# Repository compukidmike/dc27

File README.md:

# Here's all the design files for both badges we made for Defcon 27

# Kit assembly instructions for the Fifth Element badges are [here](https://github.com/compukidmike/dc27/tree/master/Fifth%20Element%20Badge).

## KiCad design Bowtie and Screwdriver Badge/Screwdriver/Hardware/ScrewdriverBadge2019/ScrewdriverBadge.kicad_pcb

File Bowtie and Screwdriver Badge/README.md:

# Here's all the code and KiCad files for the BowTie and Screwdriver badge for Defcon 27

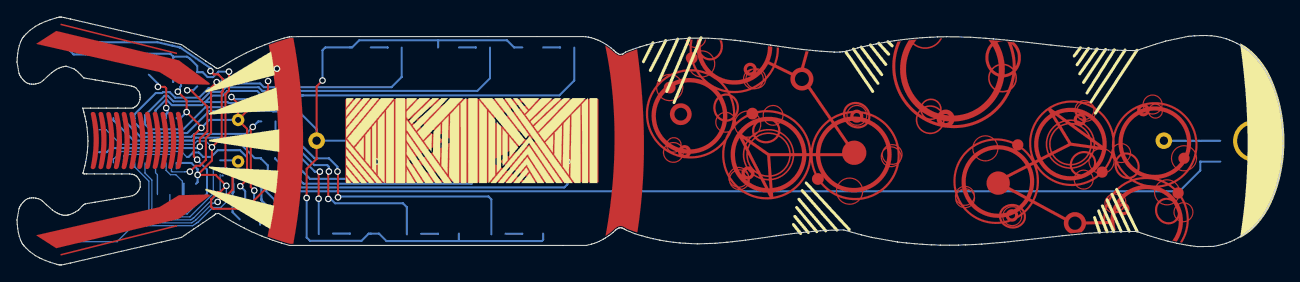
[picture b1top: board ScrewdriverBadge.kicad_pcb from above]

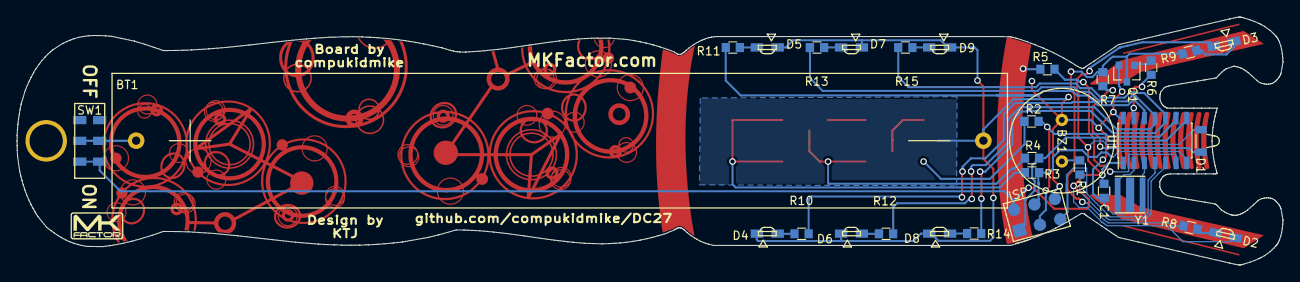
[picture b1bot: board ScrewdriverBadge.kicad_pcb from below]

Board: 2 copper layers, 152.4 x 29.9 mm, 33 parts (32 on the bottom side), 27 nets.

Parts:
BT1: Battery; Battery-2AA-BC12AAPC
BZ1: Buzzer; Buzzer-12.6mm-Murata-PKM13EPYH4000
C1: 0.1uF; R_0603_Mid
D1: LED; LED-IR-RA-OSRAM-SFH-4045N
D2, D3, D4, D5, D6, D7, D8, D9: LED; LTST-S220-LED-RA
ISP: AVR-ISP-6; ISP-AVR-6Pin-SMD
Q1: BC817; SOT-23
R1, R2, R3, R4, R5, R6, R7, R8, R9, R10, R11, R12, R13, R14, R15: R; R_0603_Mid
Ref**: Val**; drawing
SW1: SW_SPST; JS202011JCQN
U1: ATTINY84A-SSU; SOIC-14_3.9x8.7mm_Pitch1.27mm
Y1: Resonator; Resonator-AWSCR-3.7x3.1mm

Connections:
+BATT: C1.1, D1.2, D2.2, D3.2, ISP.2, SW1.1, U1.1
BUZZ: R1.2, U1.5
GND: BT1.2, BZ1.2, C1.2, D4.1, D5.1, D6.1, D7.1, D8.1, D9.1, ISP.6, Q1.2, U1.14, Y1.2
IRLED: R6.2, U1.13
LED1: R10.2, R11.2, U1.12
LED2: R12.2, R13.2, U1.11
LED3: R14.2, R15.2, U1.10
MISO: ISP.1, R3.2, U1.8
MOSI: ISP.4, R4.2, U1.7
unnamed: BT1.1, SW1.2
unnamed: BZ1.1, R1.1
unnamed: D1.1, R7.2
unnamed: D2.1, R8.2
unnamed: D3.1, R9.2
unnamed: D4.2, R10.1
unnamed: D5.2, R11.1
unnamed: D6.2, R12.1
unnamed: D7.2, R13.1
unnamed: D8.2, R14.1
unnamed: D9.2, R15.1
unnamed: Q1.1, R6.1
unnamed: Q1.3, R7.1, R8.1, R9.1
unnamed: R5.2, U1.6
unnamed: U1.2, Y1.3
unnamed: U1.3, Y1.1
RST: ISP.5, U1.4
SCK: ISP.3, R2.2, U1.9

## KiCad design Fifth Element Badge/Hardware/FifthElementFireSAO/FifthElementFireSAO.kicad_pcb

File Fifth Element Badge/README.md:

# Badge Usage
The badge has 2 modes: Bling and Movie. Change modes by pressing the mode button on the back.
Bling mode simply flashes the LEDs.
Movie mode only lights up when you get all 4 stones placed in the correct positions on the badge.

##Stone Retention Strings
We included 4 strings with the badges. These are for tying to the stones so that they can be attached to the badge and not get lost. The stones are heavy and have a tendancy to fall off the badge when worn.

To use the strings, tie them in a loop through the hole in the bottom of the stone. Feed that loop through the small holes in the badge near each stone connector. Then connect the string to the lanyard clip behind the badge. There are two different lengths of string. This is because two of the stones are closer to the lanyard holes. Make sure to put the strings on the correct stones based on their position.

# Kit Assembly Instructions
You will need the following to assemble the element stones:
- Soldering Iron
- Solder
- Tweezers

Here's a video that shows how to assemble the stones:
https://youtu.be/dvJu6TR9gxQ

The resistor packs are color coded and each resistor has a number on it:

| Color | Resistor Value | Number on Resistor | Quantity |
| --- | :---: | :---: | :---: |
| No Color | 10 | 100 | 1 |
| Green | 51 | 510 | 3 |
| Blue | 2k | 202 | 2 |
| Pink | 3.9k | 3901 | 2 |
| Orange | 6.2k | 622 | 2 |
| Yellow | 8.2k | 822 | 2 |

The LEDs have colored stickers on them for Red, Yellow, Green, Blue.

# Badges Available
We had some left after Defcon, so if you're interested in getting a Fifth Element badge, we have some available at https://www.tindie.com/products/compukidmike/fifth-element-stones-badge-from-defcon-27/

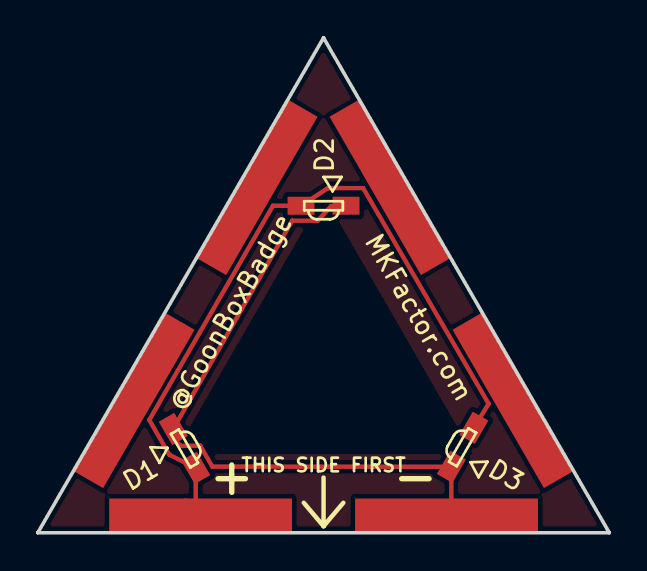
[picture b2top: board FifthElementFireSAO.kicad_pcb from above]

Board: 2 copper layers, 31.8 x 27.5 mm, 6 parts (0 on the bottom side), 2 nets.

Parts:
BT1, BT2, BT3: Battery_Cell; FifthElementB2BBottomConnector
D1, D2, D3: LED; LTST-S220-LED-RA

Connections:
unnamed: BT1.1, BT2.1, BT3.1, D1.2, D2.2, D3.2
unnamed: BT1.2, BT2.2, BT3.2, D1.1, D2.1, D3.1

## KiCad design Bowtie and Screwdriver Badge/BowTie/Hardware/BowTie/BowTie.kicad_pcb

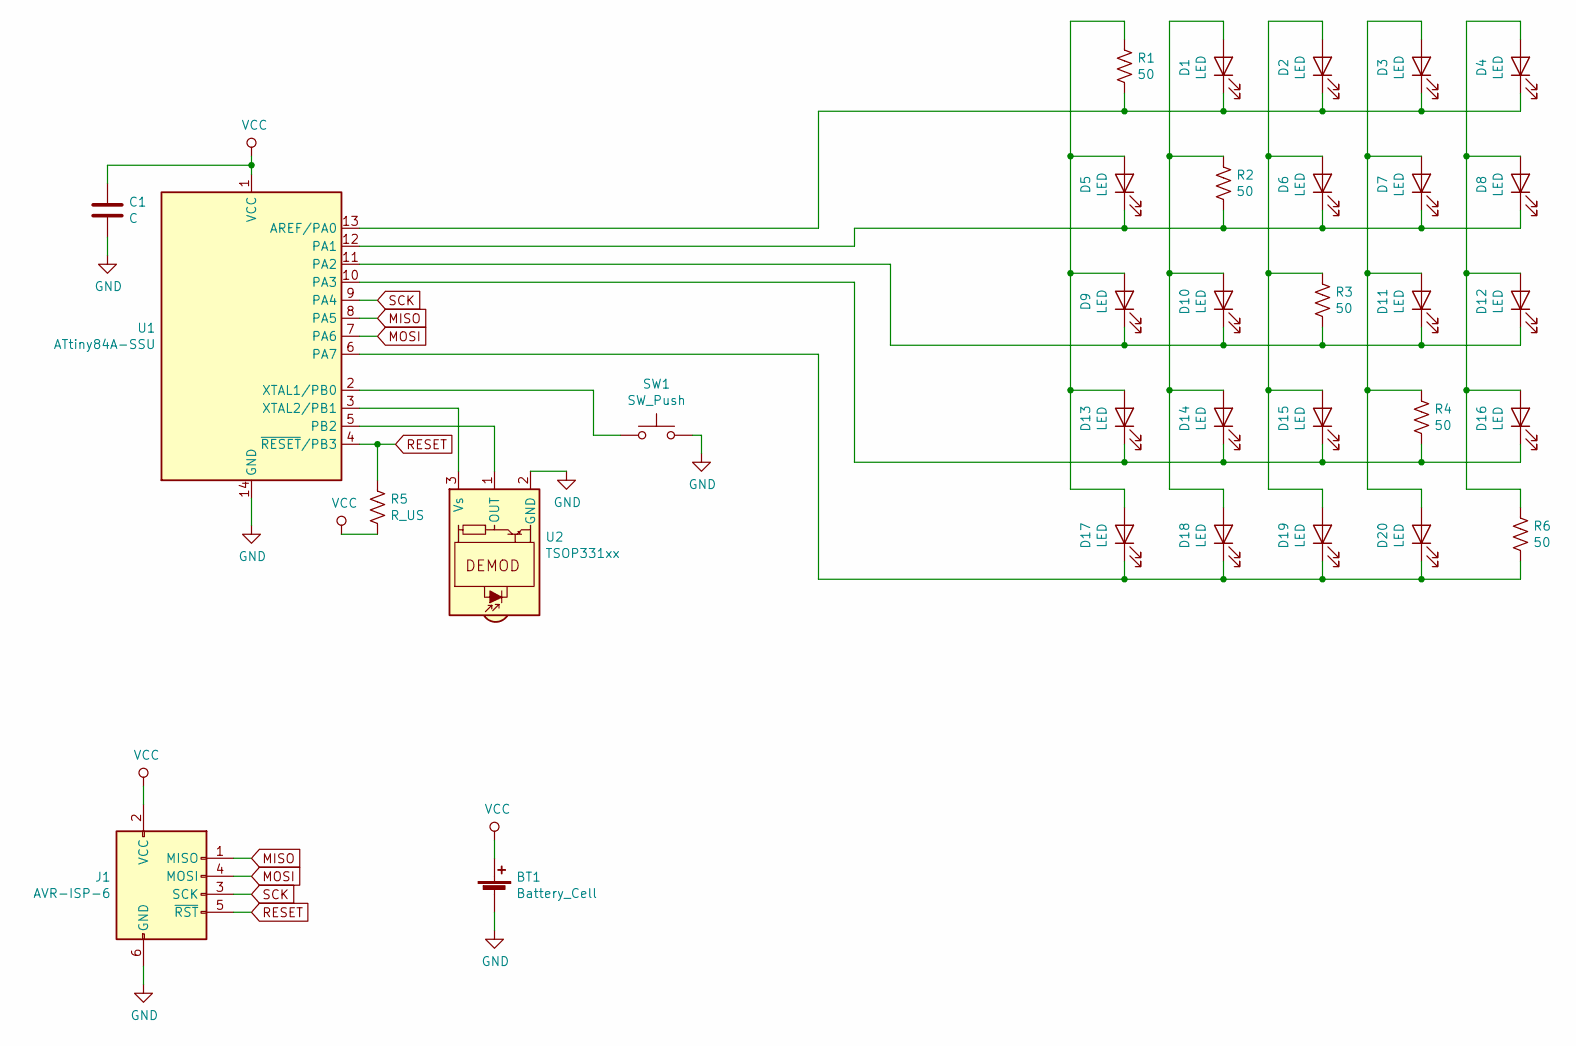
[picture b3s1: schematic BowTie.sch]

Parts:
BT1: Battery_Cell; Linx-BAT-HLD-001
C1: C; C_0603
D1, D2, D3, D4, D5, D6, D7, D8, D9, D10, D11, D12, D13, D14, D15, D16, D17, D18, D19, D20: LED; LED_0603
J1: AVR-ISP-6; ISP-AVR-6Pin-SMD
R1, R2, R3, R4, R6: 50; R_0603
R5: R_US; R_0603
SW1: SW_Push; SW_SPST_PTS645
U1: ATtiny84A-SSU; SOIC-14_3.9x8.7mm_Pitch1.27mm
U2: TSOP331xx; TSOP332-IR-RCV

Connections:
GND: BT1.2 (-), C1.2, J1.6 (GND), SW1.2, U1.14 (GND), U2.2 (GND)
MISO: J1.1 (MISO), U1.8 (PA5)
MOSI: J1.4 (MOSI), U1.7 (PA6)
unnamed: D1.1 (K), D2.1 (K), D3.1 (K), D4.1 (K), R1.2, U1.13 (AREF/PA0)
unnamed: D1.2 (A), D10.2 (A), D14.2 (A), D18.2 (A), R2.1
unnamed: D5.1 (K), D6.1 (K), D7.1 (K), D8.1 (K), R2.2, U1.12 (PA1)
unnamed: D9.1 (K), D10.1 (K), D11.1 (K), D12.1 (K), R3.2, U1.11 (PA2)
unnamed: D3.2 (A), D7.2 (A), D11.2 (A), D20.2 (A), R4.1
unnamed: D4.2 (A), D8.2 (A), D12.2 (A), D16.2 (A), R6.1
unnamed: D13.1 (K), D14.1 (K), D15.1 (K), D16.1 (K), R4.2, U1.10 (PA3)
unnamed: D5.2 (A), D9.2 (A), D13.2 (A), D17.2 (A), R1.1
unnamed: D2.2 (A), D6.2 (A), D15.2 (A), D19.2 (A), R3.1
unnamed: D17.1 (K), D18.1 (K), D19.1 (K), D20.1 (K), R6.2, U1.6 (PA7)
unnamed: SW1.1, U1.2 (XTAL1/PB0)
unnamed: U1.3 (XTAL2/PB1), U2.3 (Vs)
unnamed: U1.5 (PB2), U2.1 (OUT)
RESET: J1.5 (~RST), R5.1, U1.4 (~RESET~/PB3)
SCK: J1.3 (SCK), U1.9 (PA4)
VCC: BT1.1 (+), C1.1, J1.2 (VCC), R5.2, U1.1 (VCC)

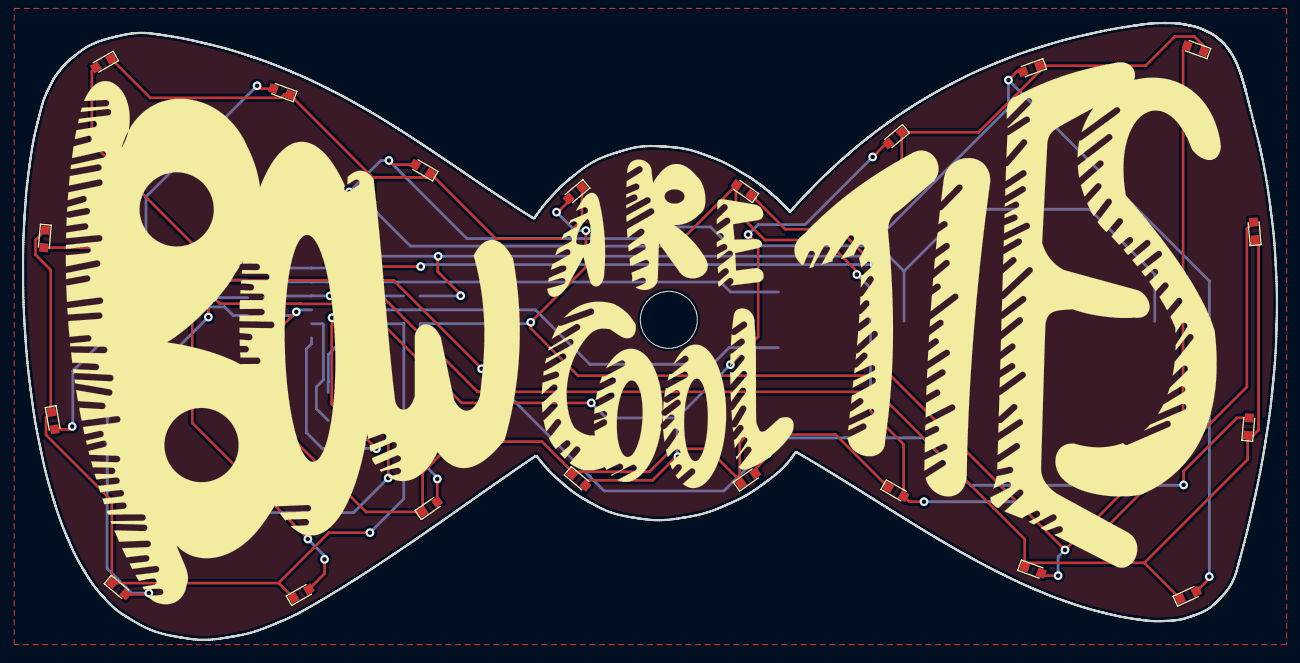
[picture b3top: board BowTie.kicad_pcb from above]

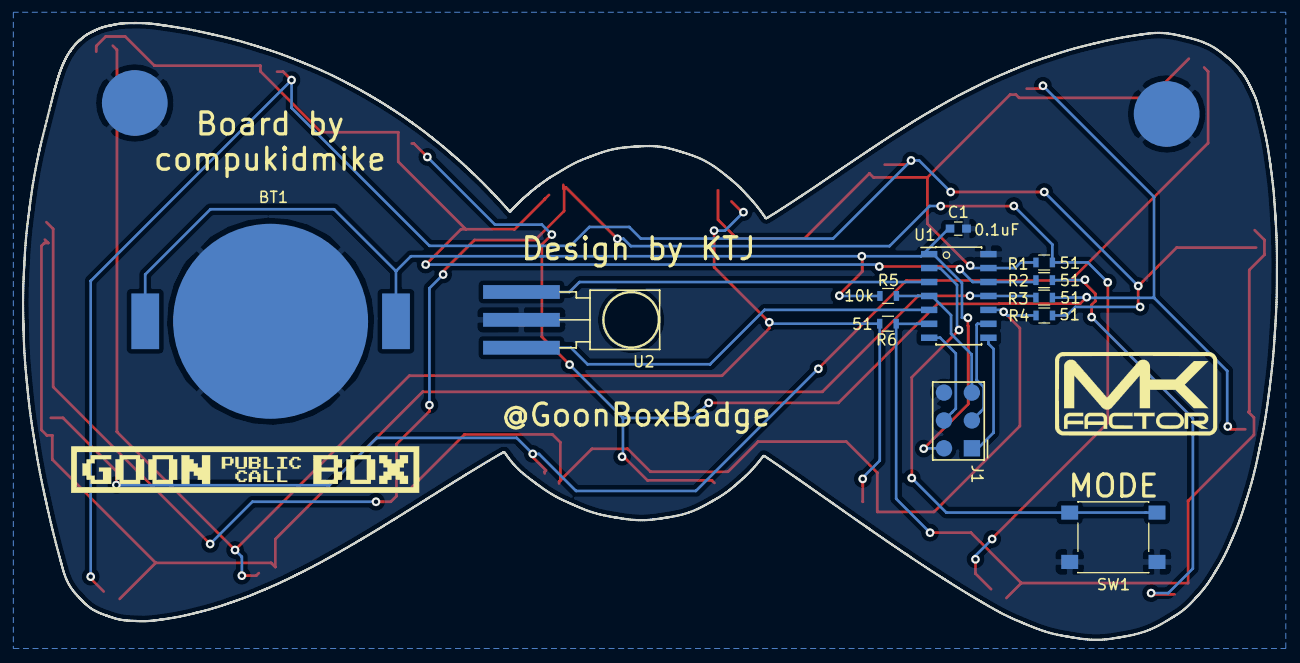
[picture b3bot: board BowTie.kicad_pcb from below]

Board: 2 copper layers, 114.3 x 56.2 mm, 32 parts (12 on the bottom side), 19 nets.

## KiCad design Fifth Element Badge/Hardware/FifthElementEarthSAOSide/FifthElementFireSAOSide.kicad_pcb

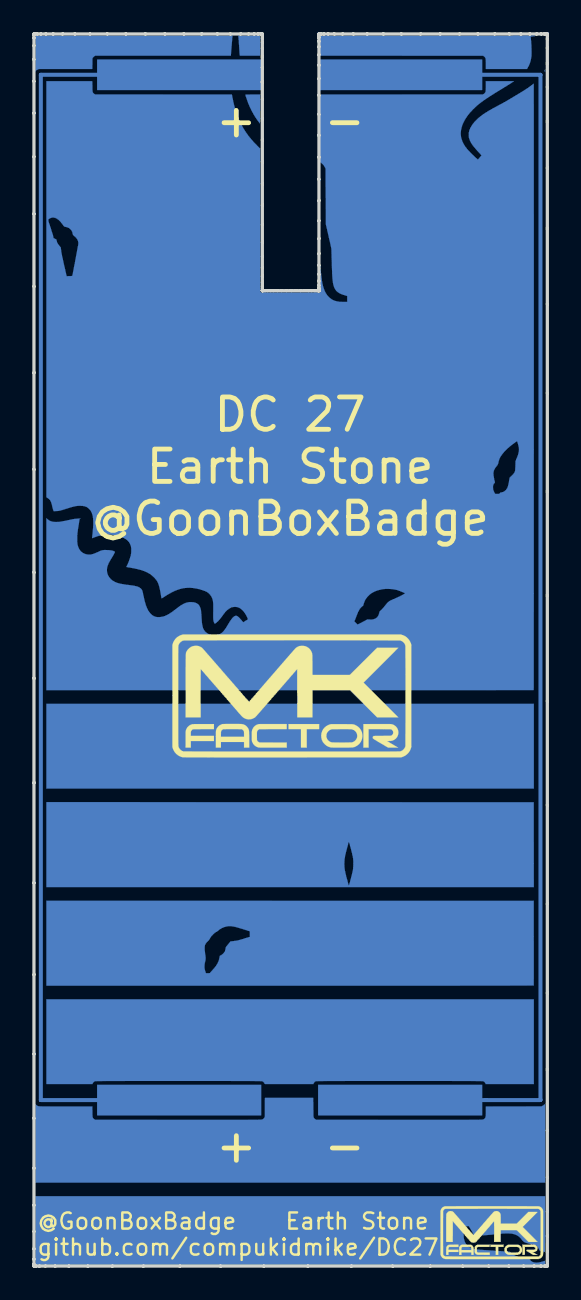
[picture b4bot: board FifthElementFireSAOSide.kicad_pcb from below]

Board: 2 copper layers, 31.8 x 76.2 mm, 3 parts (2 on the bottom side), 2 nets.

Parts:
BT1, BT2: Battery_Cell; FifthElementB2BConnector
Ref**: Val**; EarthSide

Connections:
unnamed: BT1.2, BT2.2
unnamed: BT1.1, BT2.1

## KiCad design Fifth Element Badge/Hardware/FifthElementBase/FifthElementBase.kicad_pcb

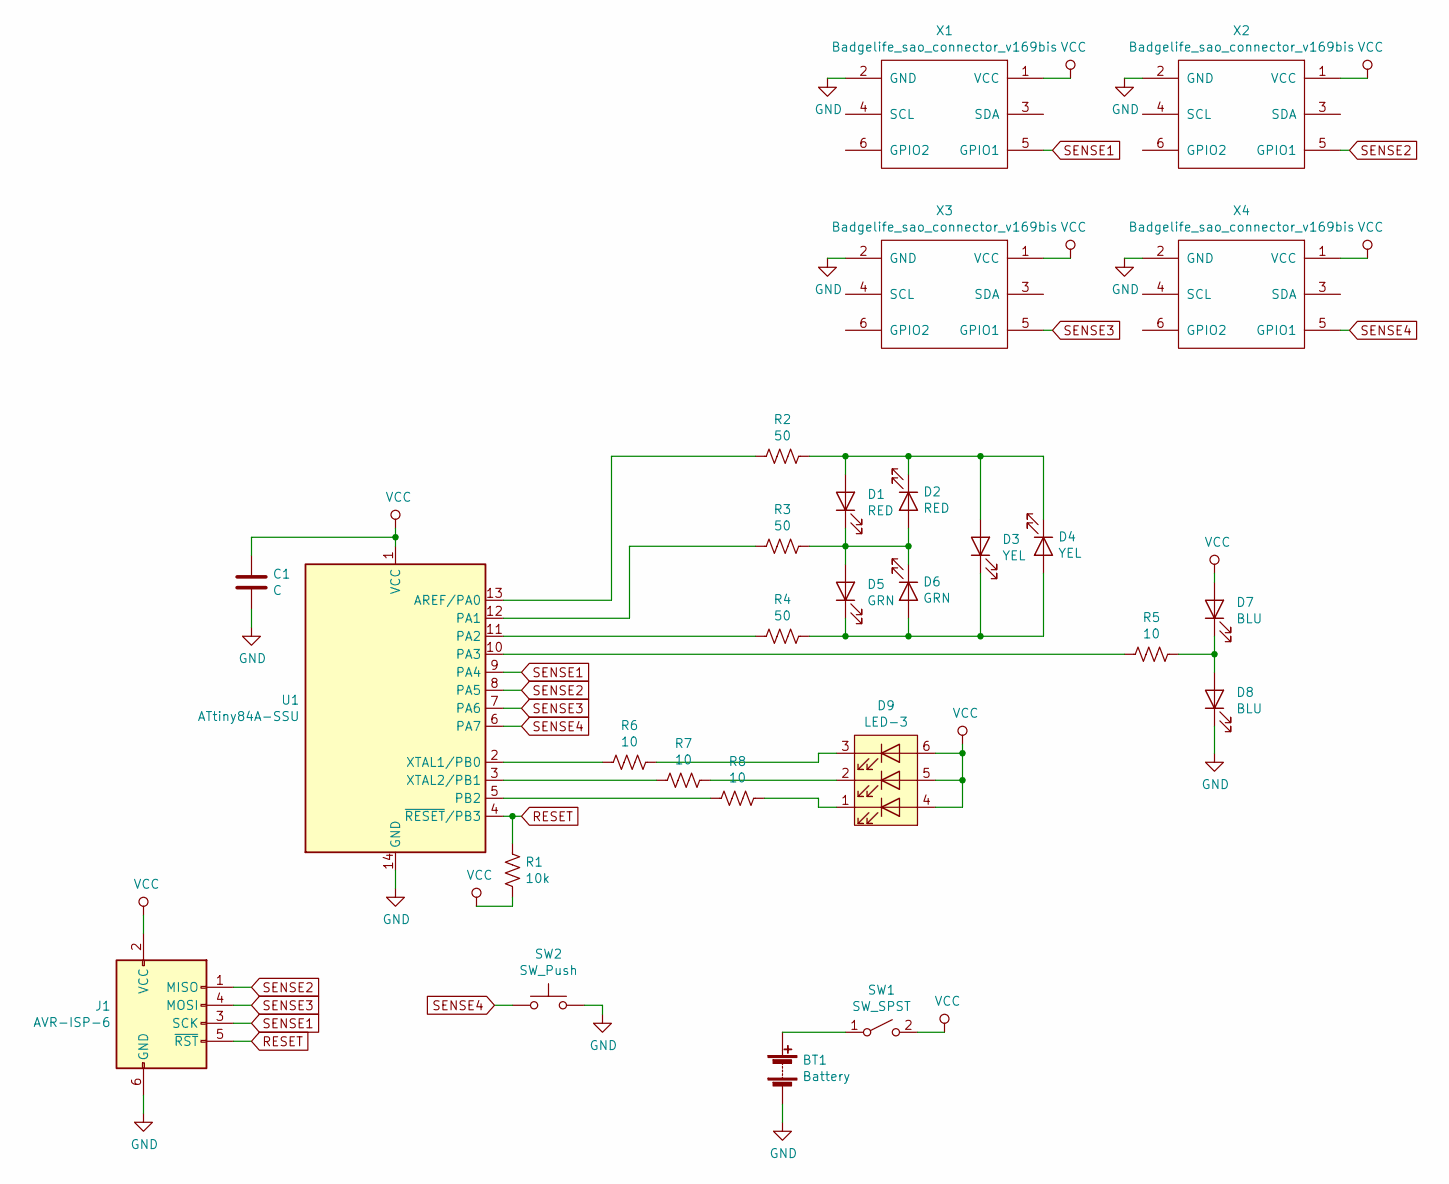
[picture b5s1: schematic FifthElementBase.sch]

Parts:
BT1: Battery; Battery-WireConn-SMD
C1: C; C_0805_HandSoldering
D1, D2: RED; LTST-S220-LED-RA
D3, D4: YEL; LTST-S220-LED-RA
D5, D6: GRN; LTST-S220-LED-RA
D7, D8: BLU; LTST-S220-LED-RA
D9: LED-3; 61-238_XK2C-LED-6PLCC
J1: AVR-ISP-6; ISP-AVR-6Pin-SMD
R1: 10k; R_0805_HandSoldering
R2, R3, R4: 50; R_0805_HandSoldering
R5, R6, R7, R8: 10; R_0805_HandSoldering
SW1: SW_SPST; JS102011SAQN
SW2: SW_Push; SW_SPST_PTS645
U1: ATtiny84A-SSU; SOIC-14_3.9x8.7mm_Pitch1.27mm
X1, X2, X3, X4: Badgelife_sao_connector_v169bis; Badgelife-SAOv169-BADGE-2x3

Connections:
GND: BT1.2 (-), C1.2, D8.1 (K), J1.6 (GND), SW2.2, U1.14 (GND), X1.2 (GND), X2.2 (GND), X3.2 (GND), X4.2 (GND)
unnamed: BT1.1 (+), SW1.1 (A)
unnamed: D1.1 (K), D2.2 (A), D5.2 (A), D6.1 (K), R3.1
unnamed: D1.2 (A), D2.1 (K), D3.2 (A), D4.1 (K), R2.1
unnamed: D3.1 (K), D4.2 (A), D5.1 (K), D6.2 (A), R4.1
unnamed: D7.1 (K), D8.2 (A), R5.1
unnamed: D9.1 (K), R8.1
unnamed: D9.2 (K), R7.1
unnamed: D9.3 (K), R6.1
unnamed: R2.2, U1.13 (AREF/PA0)
unnamed: R3.2, U1.12 (PA1)
unnamed: R4.2, U1.11 (PA2)
unnamed: R5.2, U1.10 (PA3)
unnamed: R6.2, U1.2 (XTAL1/PB0)
unnamed: R7.2, U1.3 (XTAL2/PB1)
unnamed: R8.2, U1.5 (PB2)
RESET: J1.5 (~RST), R1.1, U1.4 (~RESET~/PB3)
SENSE1: J1.3 (SCK), U1.9 (PA4), X1.5 (GPIO1)
SENSE2: J1.1 (MISO), U1.8 (PA5), X2.5 (GPIO1)
SENSE3: J1.4 (MOSI), U1.7 (PA6), X3.5 (GPIO1)
SENSE4: SW2.1, U1.6 (PA7), X4.5 (GPIO1)
VCC: C1.1, D7.2 (A), D9.4 (A), D9.5 (A), D9.6 (A), J1.2 (VCC), R1.2, SW1.2 (B), U1.1 (VCC), X1.1 (VCC), X2.1 (VCC), X3.1 (VCC), X4.1 (VCC)

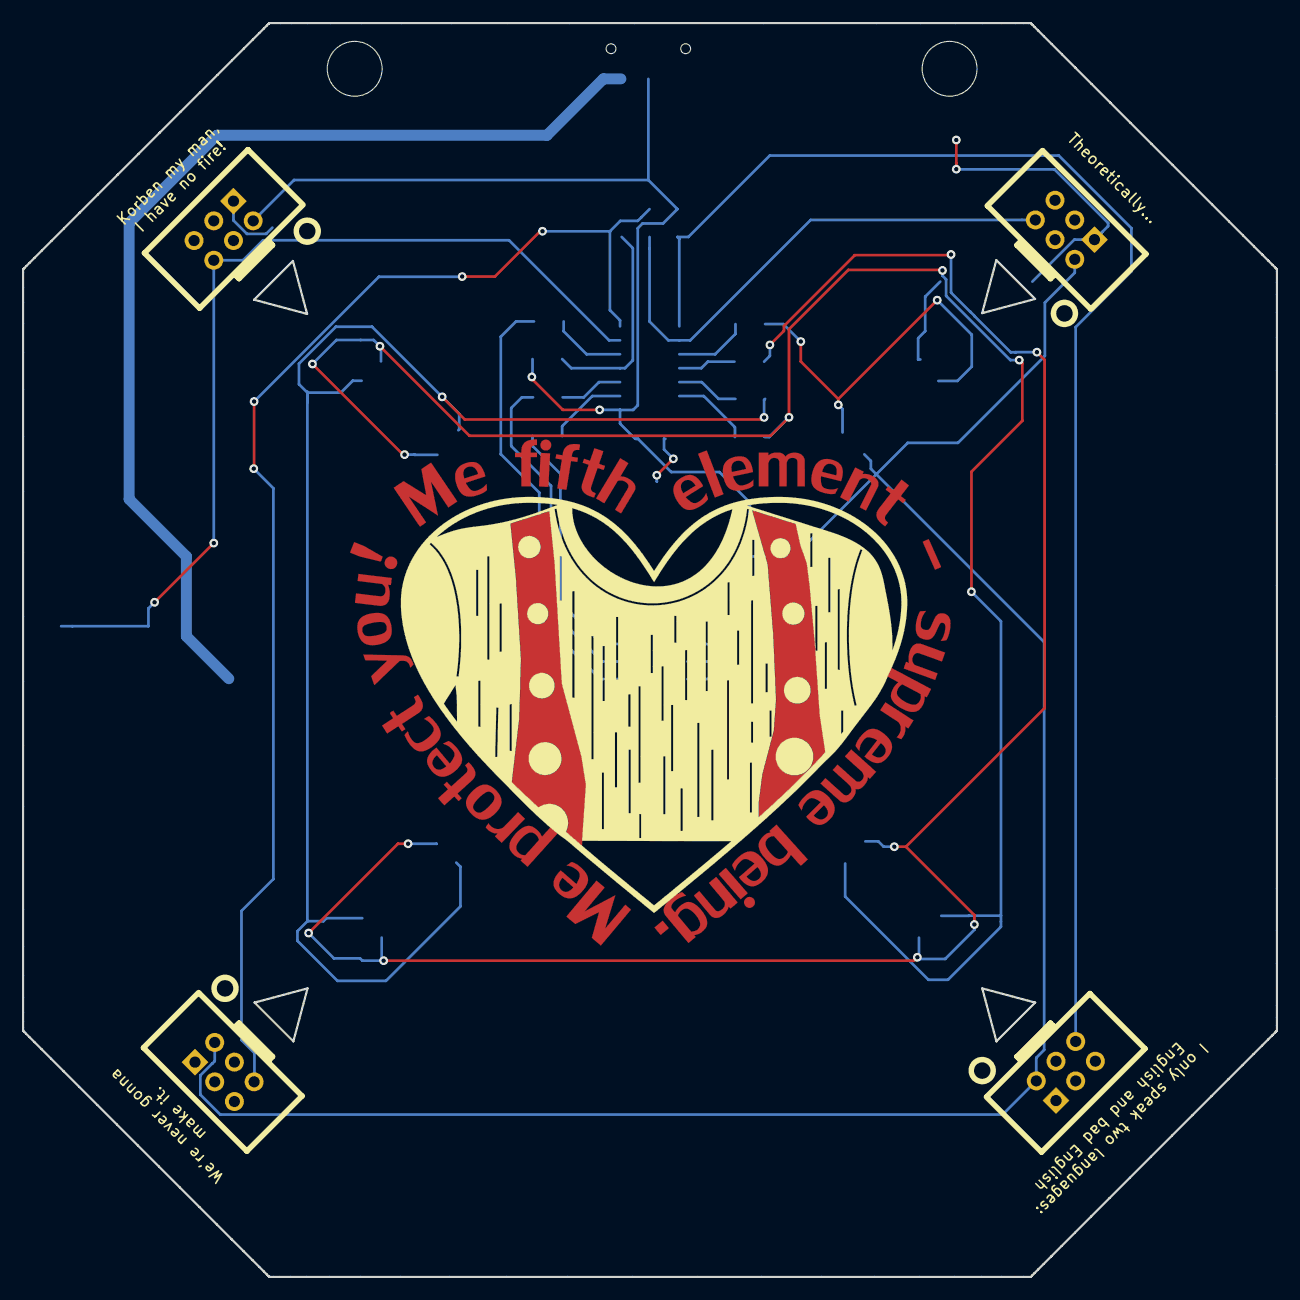
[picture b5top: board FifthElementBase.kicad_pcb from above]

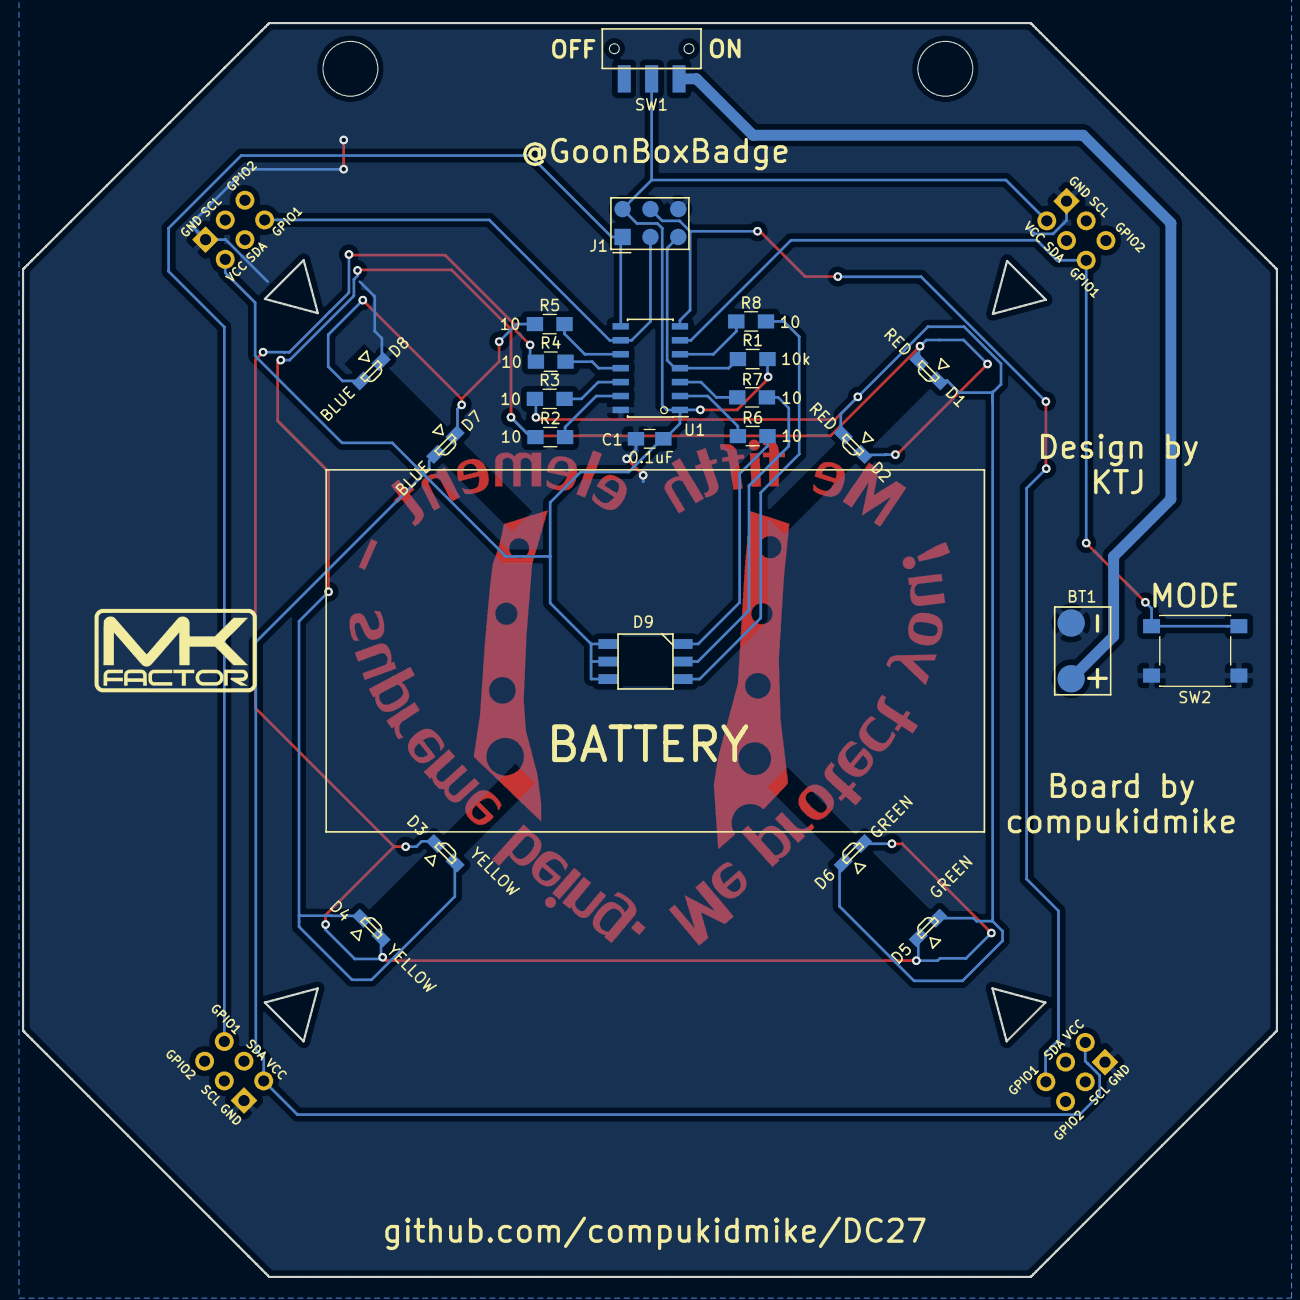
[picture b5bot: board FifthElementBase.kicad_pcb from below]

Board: 2 copper layers, 114.3 x 114.3 mm, 27 parts (23 on the bottom side), 22 nets.

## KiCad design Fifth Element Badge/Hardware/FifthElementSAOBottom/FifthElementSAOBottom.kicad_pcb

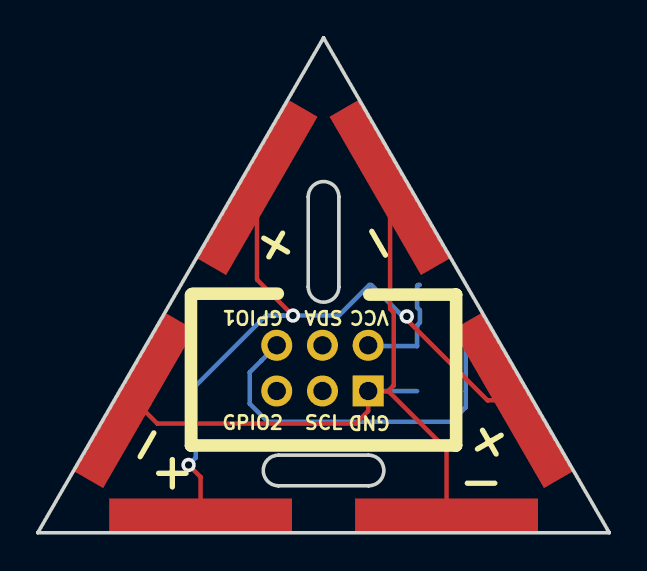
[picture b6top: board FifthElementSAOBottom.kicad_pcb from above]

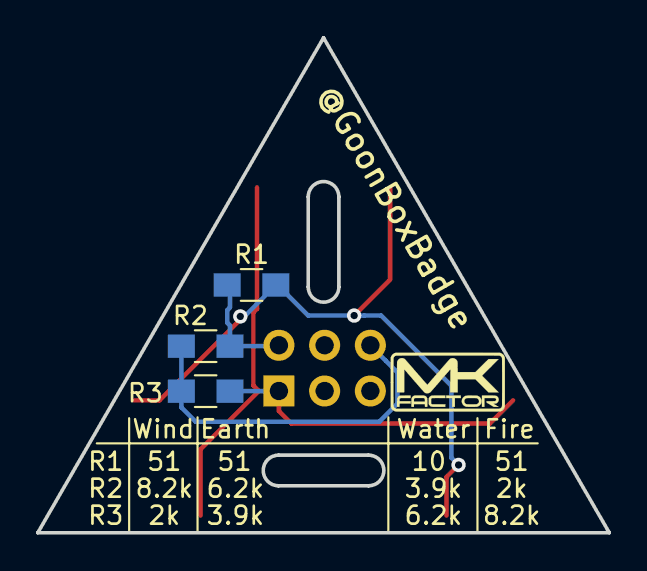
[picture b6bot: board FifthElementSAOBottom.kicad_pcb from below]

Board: 2 copper layers, 31.8 x 27.5 mm, 7 parts (4 on the bottom side), 4 nets.

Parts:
BT1, BT2, BT3: Battery_Cell; FifthElementB2BBottomConnector
R1, R2, R3: R_US; R_0805_HandSoldering
X1: Badgelife_sao_connector_v169bis; Badgelife-SAOv169-SAO-2x3

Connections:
unnamed: BT1.1, BT2.1, BT3.1, R1.2
unnamed: BT1.2, BT2.2, BT3.2, R3.2, X1.2
unnamed: R1.1, R2.1, X1.1
unnamed: R2.2, R3.1, X1.5

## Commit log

2019-07-26 Readme update
2019-12-31 Upload Design Files
